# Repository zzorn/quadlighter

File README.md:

quadlighter
===========

Led PWM light controller board

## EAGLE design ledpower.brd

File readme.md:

quadlighter
===========

Led PWM light controller board.

Contains Eagle scematics and board layout.

Uses I2C bus controllable PCA9685 and two ULN2803 darlington arrays.

Has outputs for four RGB led strips, and four extra 12V PWM outputs (e.g. small powerled, fans, or such).

Use the solder jumpers to configure the I2C address of a device before use (either the 0 or 1 solder pad must be bridged for each address byte).

License: Creative Commons share alike non commercial.

zzorn at iki dot fi

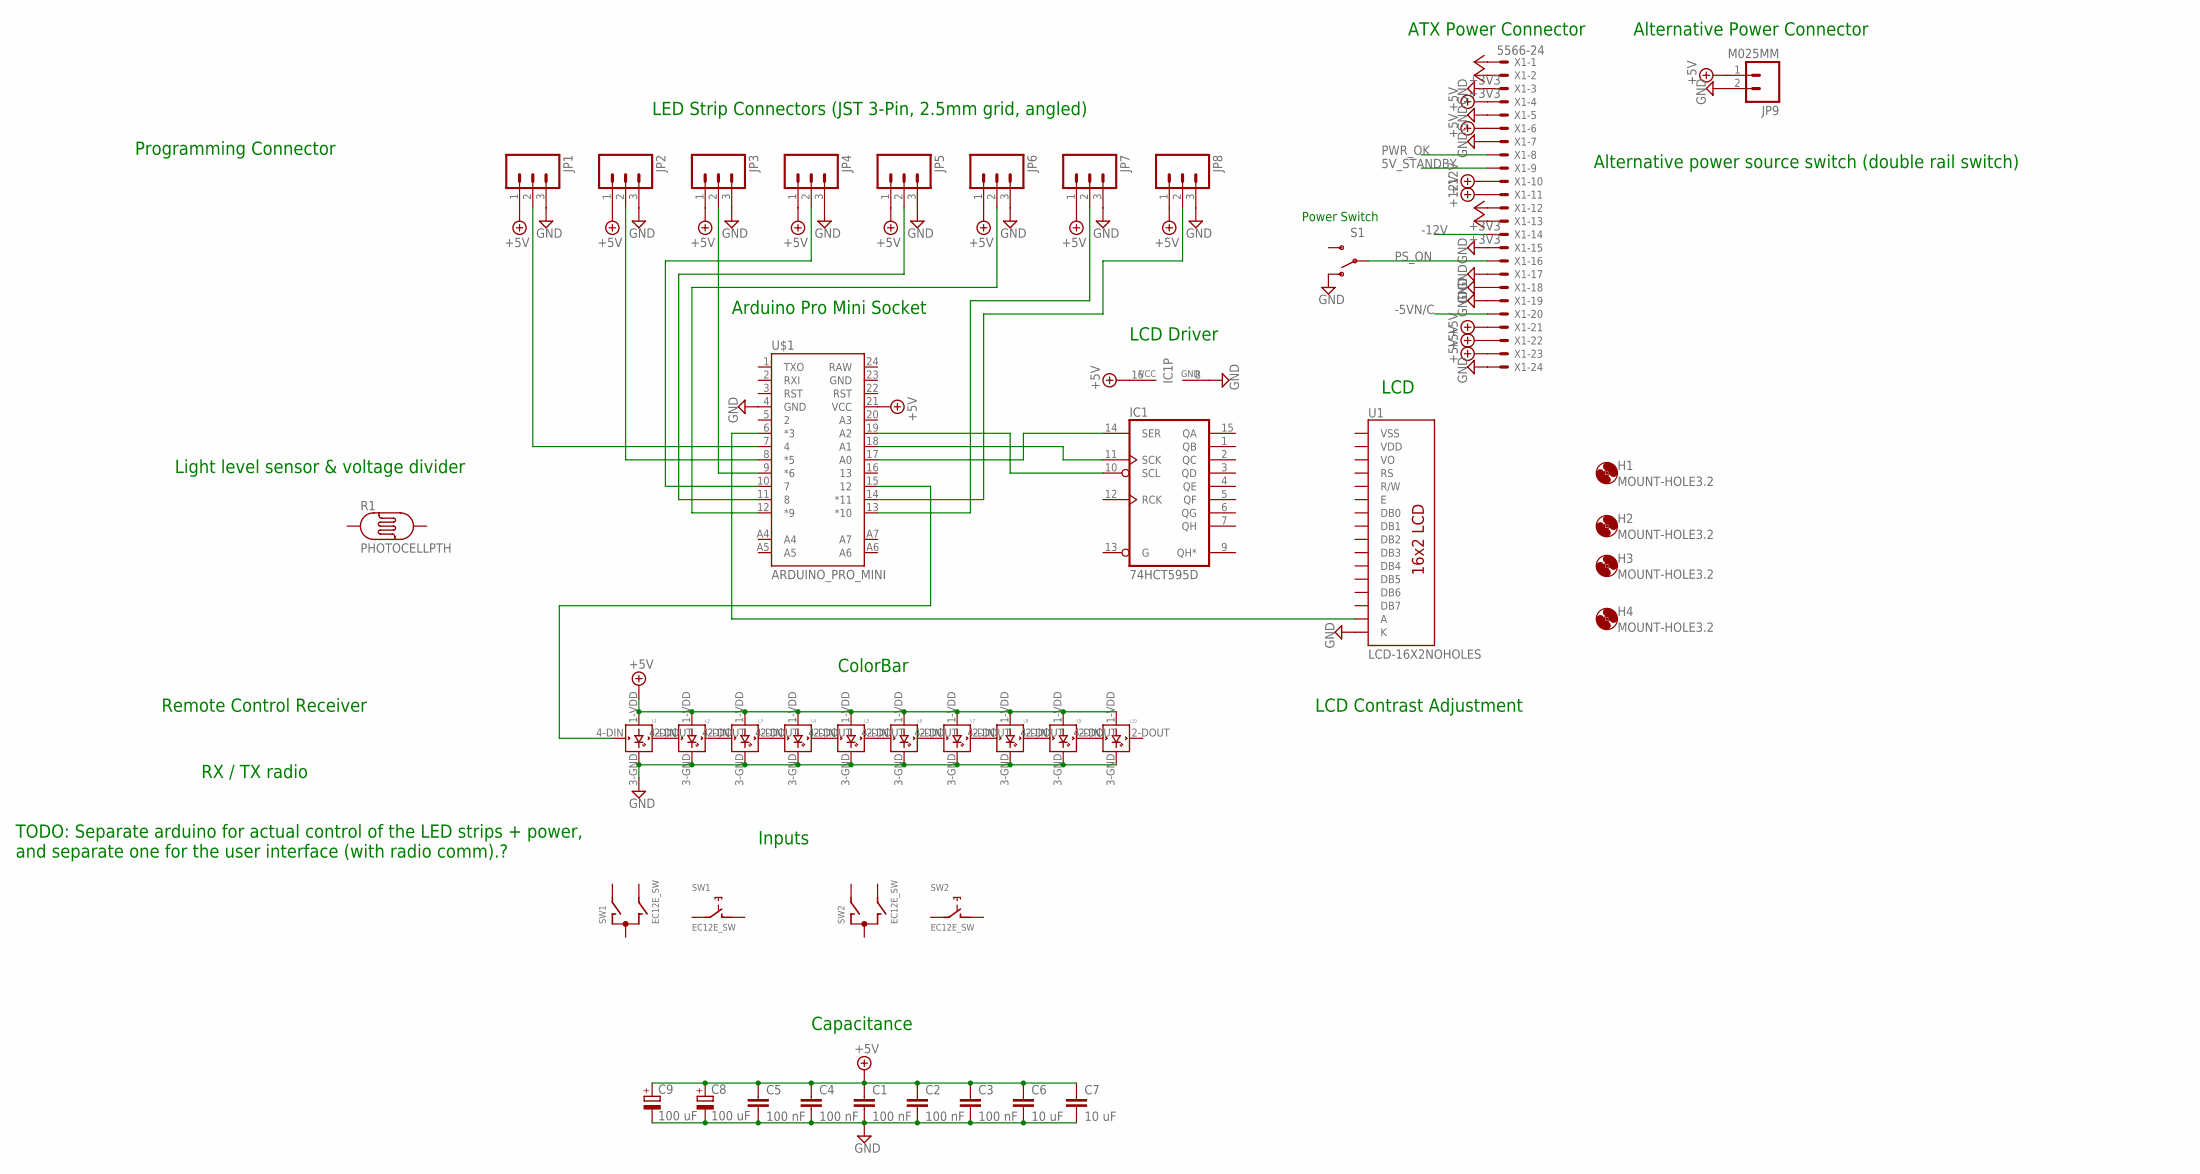
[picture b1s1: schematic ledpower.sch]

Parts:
C1, C2, C3, C4, C5: 100 nF; C0805
C6, C7: 10 uF; C1206
C8, C9: 100 uF; E3,5-10
H1, H2, H3, H4: MOUNT-HOLE3.2; 3,2
IC1: 74HCT595D; SO16
JP1, JP2, JP3, JP4, JP5, JP6, JP7, JP8: M03LONGPADS; 1X03_LONGPADS
JP9: M025MM; SCREWTERMINAL-5MM-2
L1, L2, L3, L4, L5, L6, L7, L8, L9, L10: WS2812B
R1: PHOTOCELLPTH; PHOTOCELL
S1: SWITCH-SPSTPTH; SWITCH-SPDT
SW1, SW2: EC12E_SW; ALPS_EC12E_SW
U1: LCD-16X2NOHOLES; LCD-16X2_NOHOLES
U$1: ARDUINO_PRO_MINI
X1: 5566-24

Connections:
5V_STANDBY: X1.9
+3V3: X1.1, X1.2, X1.12, X1.13
+5V: C1.1, C2.1, C3.1, C4.1, C5.1, C6.1, C7.1, C8.+, C9.+, IC1.16 (VCC), JP1.1, JP2.1, JP3.1, JP4.1, JP5.1, JP6.1, JP7.1, JP8.1, JP9.1, L1.1-VDD (VDD), L2.1-VDD (VDD), L3.1-VDD (VDD), L4.1-VDD (VDD), L5.1-VDD (VDD), L6.1-VDD (VDD), L7.1-VDD (VDD), L8.1-VDD (VDD), L9.1-VDD (VDD), L10.1-VDD (VDD), U$1.21 (VCC), X1.4, X1.6, X1.21, X1.22, X1.23
+12V: X1.10, X1.11
-5VN/C: X1.20
-12V: X1.14
GND: C1.2, C2.2, C3.2, C4.2, C5.2, C6.2, C7.2, C8.-, C9.-, IC1.8 (GND), JP1.3, JP2.3, JP3.3, JP4.3, JP5.3, JP6.3, JP7.3, JP8.3, JP9.2, L1.3-GND (GND), L2.3-GND (GND), L3.3-GND (GND), L4.3-GND (GND), L5.3-GND (GND), L6.3-GND (GND), L7.3-GND (GND), L8.3-GND (GND), L9.3-GND (GND), L10.3-GND (GND), S1.1 (O), U1.16 (K), U$1.4 (GND), X1.3, X1.5, X1.7, X1.15, X1.17, X1.18, X1.19, X1.24
unnamed: L1.2-DOUT (DOUT), L2.4-DIN (DIN)
unnamed: L2.2-DOUT (DOUT), L3.4-DIN (DIN)
unnamed: L3.2-DOUT (DOUT), L4.4-DIN (DIN)
unnamed: L4.2-DOUT (DOUT), L5.4-DIN (DIN)
unnamed: L5.2-DOUT (DOUT), L6.4-DIN (DIN)
unnamed: L6.2-DOUT (DOUT), L7.4-DIN (DIN)
unnamed: L7.2-DOUT (DOUT), L8.4-DIN (DIN)
unnamed: L8.2-DOUT (DOUT), L9.4-DIN (DIN)
unnamed: L9.2-DOUT (DOUT), L10.4-DIN (DIN)
unnamed: L1.4-DIN (DIN), U$1.15 (12)
unnamed: JP1.2, U$1.7 (4)
unnamed: JP2.2, U$1.8 (*5)
unnamed: JP3.2, U$1.9 (*6)
unnamed: JP4.2, U$1.10 (7)
unnamed: JP5.2, U$1.11 (8)
unnamed: JP6.2, U$1.12 (*9)
unnamed: JP7.2, U$1.13 (*10)
unnamed: JP8.2, U$1.14 (*11)
unnamed: IC1.14 (SER), U$1.17 (A0)
unnamed: U1.15 (A), U$1.6 (*3)
unnamed: IC1.11 (SCK), U$1.18 (A1)
unnamed: IC1.10 (SCL), U$1.19 (A2)
PS_ON: S1.2, X1.16
PWR_OK: X1.8
VDD: U1.2 (VDD)
VSS: U1.1 (VSS)

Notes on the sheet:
ATX Power Connector
Arduino Pro Mini Socket
LCD
Power Switch
Capacitance
ColorBar
Inputs
LED Strip Connectors (JST 3-Pin, 2.5mm grid, angled)
Alternative Power Connector
Programming Connector
Light level sensor & voltage divider
Alternative power source switch (double rail switch)
LCD Contrast Adjustment
LCD Driver
Remote Control Receiver
RX / TX radio
TODO: Separate arduino for actual control of the LED strips + power, and separate one for the user interface (with radio comm).?

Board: 2 copper layers, 40 parts (8 on the bottom side), 27 nets, no tracks yet.

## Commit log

2012-06-16 Added schema and board layout. Updated readme.
2012-10-02 Working on new two sided version.
2012-10-02 Added rule check files for seeedstudio PCB manufacturing.
2012-10-02 Ignore temporary eagle files.
2012-10-02 Some work on the two sided board.
2012-10-04 Some work on the pcb.
2012-10-05 Work on the led controller.
2012-10-06 Board mostly done.
2012-10-06 Finishing touches.
2012-10-06 Renamed, copied to get two boards from 1 5x5 cm pcb order.
2012-10-07 Some more tuning.
2012-10-07 Final final touches.
2013-02-05 Added board for powering the leds, under construction.
2013-02-12 Work on the ledpower / control module.
2014-09-03 Working on led control board.
2014-09-03 Updated immerlighter board.
2014-09-03 Tuning placements.
2014-09-13 Added todo comments.

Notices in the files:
parts and their libraries:
SparkFun-Boards: Licensing: Creative Commons ShareAlike 4.0 International - https://creativecommons.org/licenses/by-sa/4.0
